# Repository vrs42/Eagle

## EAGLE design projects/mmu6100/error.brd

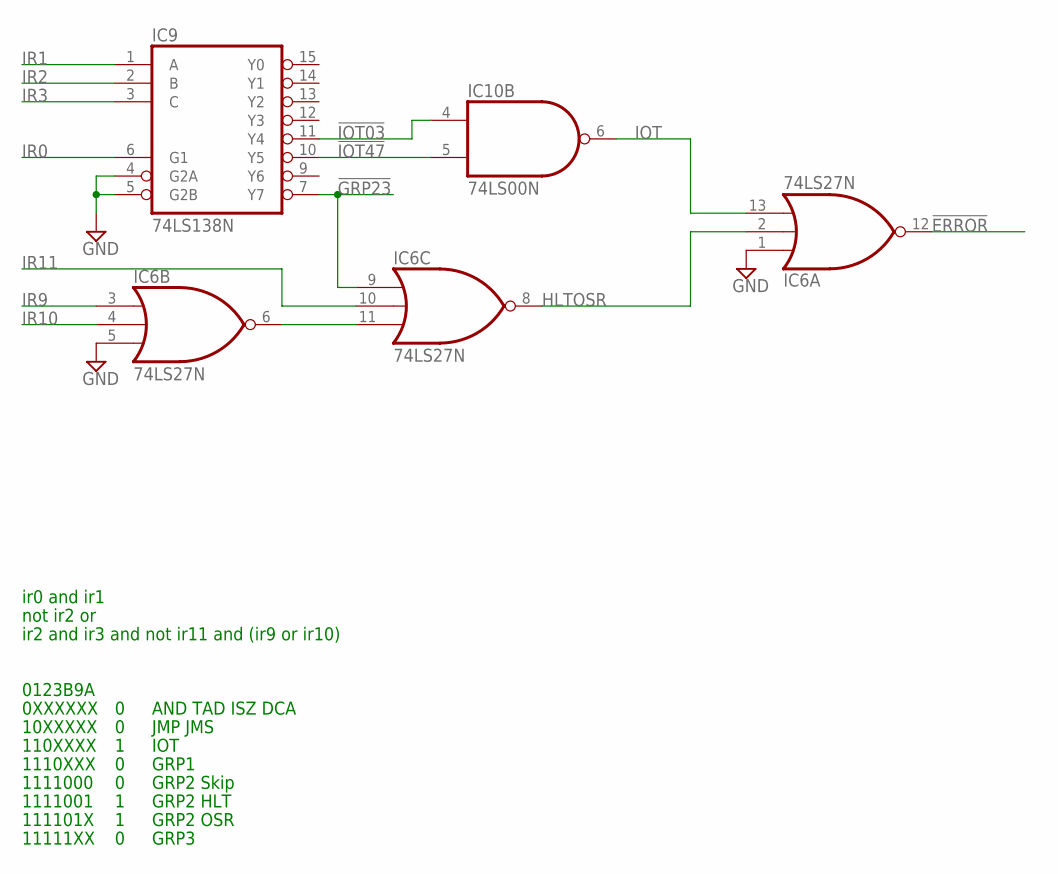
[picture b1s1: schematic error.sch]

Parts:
IC6: 74LS27N; DIL14
IC9: 74LS138N; DIL16
IC10: 74LS00N; DIL14

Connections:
!ERROR: IC6.12 (O)
!GRP23: IC6.9 (I0), IC9.7 (Y7)
!IOT03: IC9.11 (Y4), IC10.4 (I0)
!IOT47: IC9.10 (Y5), IC10.5 (I1)
GND: IC6.1 (I0), IC6.5 (I2), IC6.7 (GND), IC9.4 (G2A), IC9.5 (G2B), IC9.8 (GND), IC10.7 (GND)
HLTOSR: IC6.2 (I1), IC6.8 (O)
IOT: IC6.13 (I2), IC10.6 (O)
IR0: IC9.6 (G1)
IR1: IC9.1 (A)
IR2: IC9.2 (B)
IR3: IC9.3 (C)
IR9: IC6.3 (I0)
IR10: IC6.4 (I1)
IR11: IC6.10 (I1)
unnamed: IC6.6 (O), IC6.11 (I2)
VCC: IC6.14 (VCC), IC9.16 (VCC), IC10.14 (VCC)

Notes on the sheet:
0123B9A
0XXXXXX
10XXXXX
110XXXX
1110XXX
1111000
AND TAD ISZ DCA
JMP JMS
IOT
GRP1
GRP2 Skip
GRP2 OSR
GRP2 HLT
GRP3
1111001
111101X
11111XX
ir0 and ir1
not ir2 or
ir2 and ir3 and not ir11 and (ir9 or ir10)

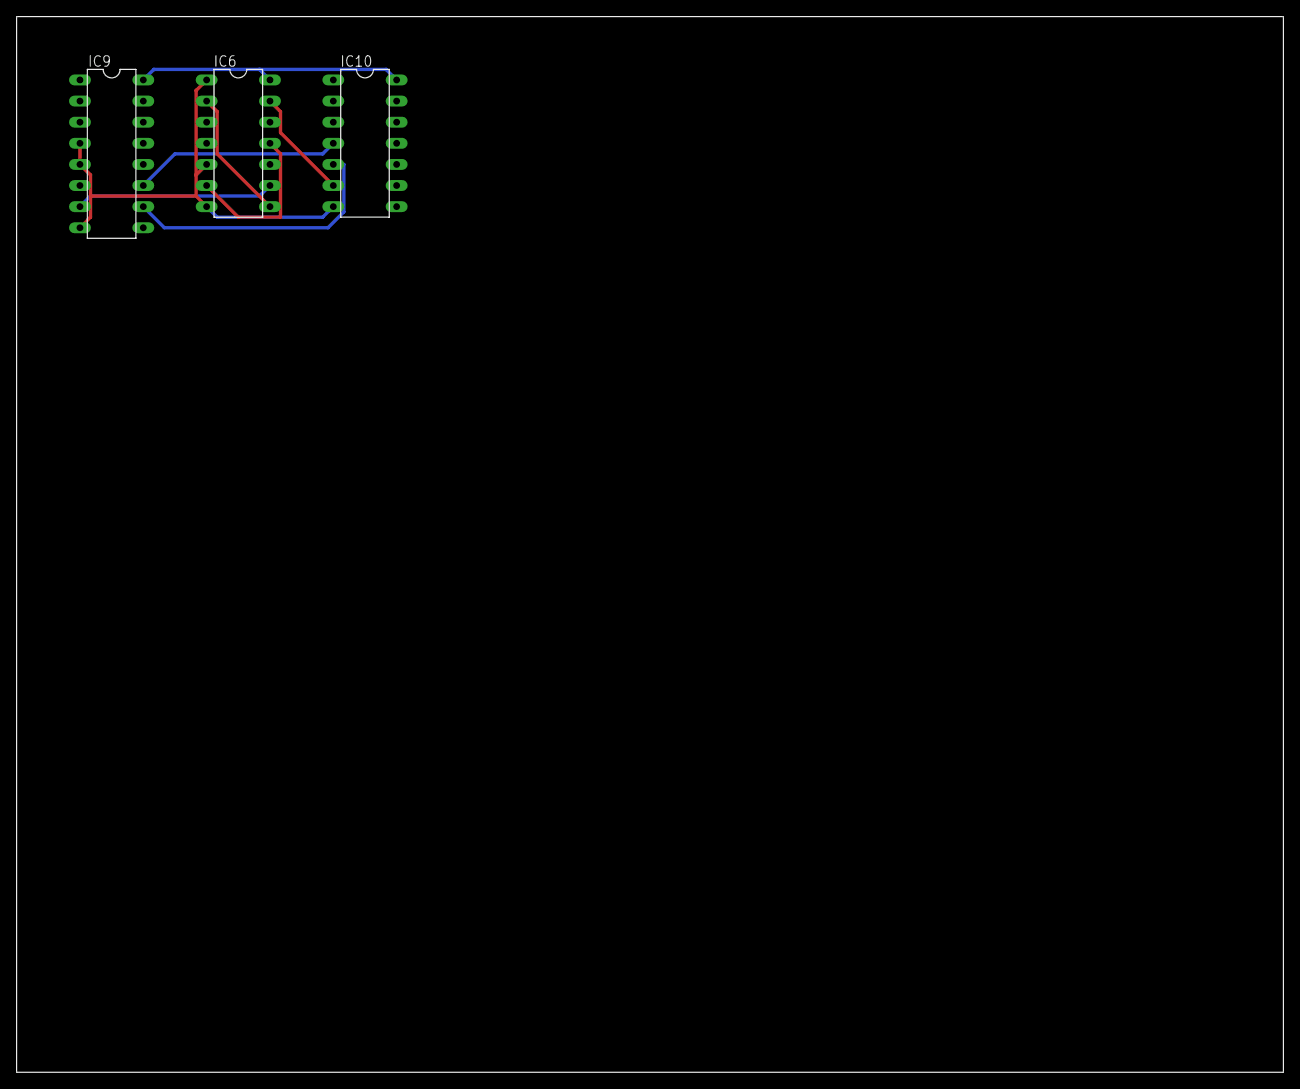
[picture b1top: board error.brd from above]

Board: 2 copper layers, 152.4 x 127.0 mm, 3 parts (0 on the bottom side), 8 nets.

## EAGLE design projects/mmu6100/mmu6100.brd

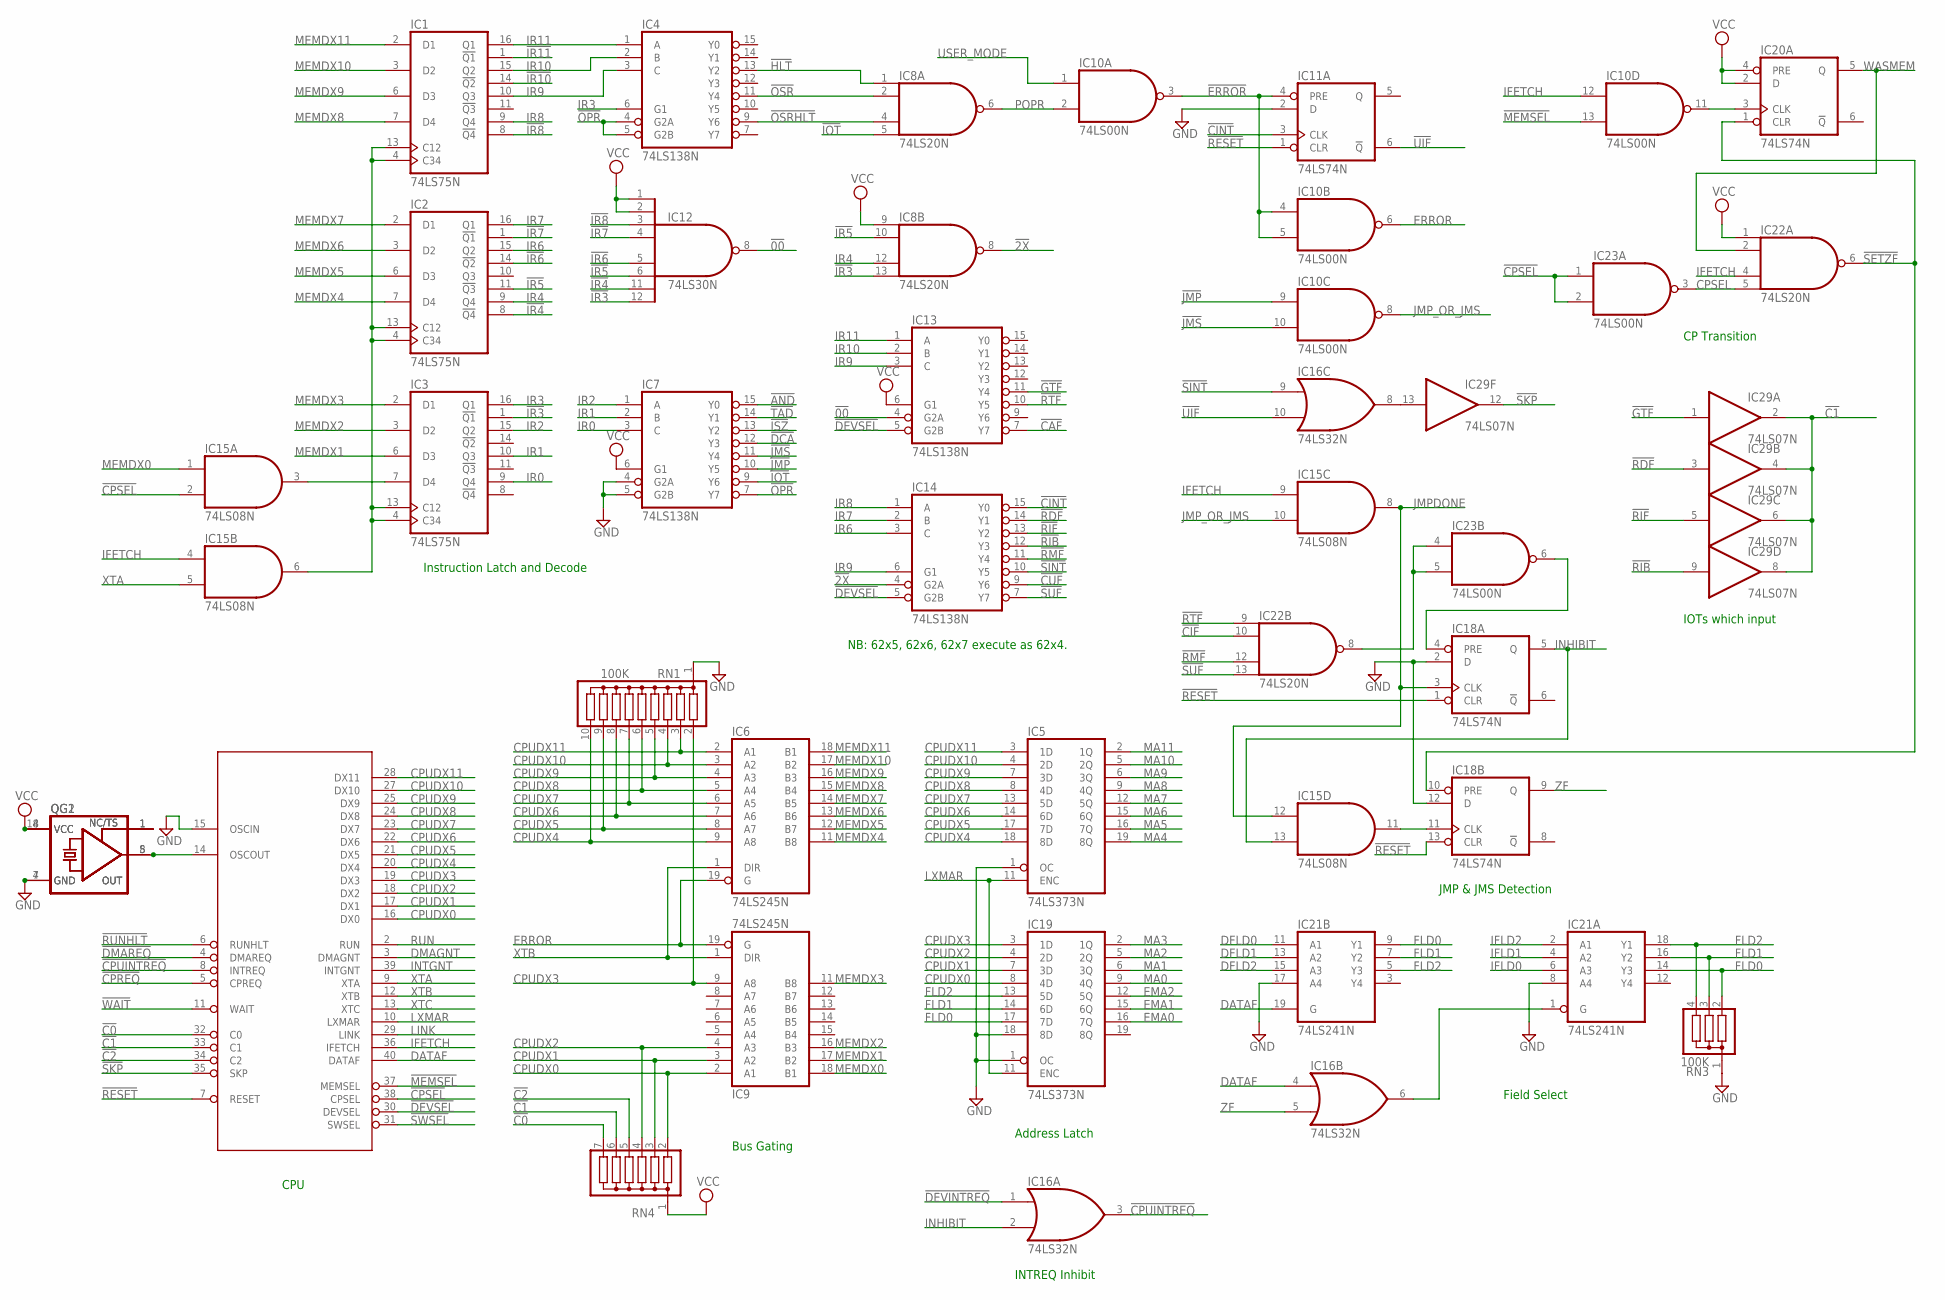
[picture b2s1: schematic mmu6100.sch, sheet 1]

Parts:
CPU: IM6100; DIL40
IC1, IC2, IC3: 74LS75N; DIL16
IC4, IC7, IC13, IC14: 74LS138N; DIL16
IC5, IC19: 74LS373N; DIL20
IC6, IC9: 74LS245N; DIL20
IC8, IC22: 74LS20N; DIL14
IC10, IC23: 74LS00N; DIL14
IC11, IC18, IC20: 74LS74N; DIL14
IC12: 74LS30N; DIL14
IC15: 74LS08N; DIL14
IC16: 74LS32N; DIL14
IC21: 74LS241N; DIL20
IC29: 74LS07N; DIL14
QG1: XO-8; DIL08S
QG2: XO-14; DIL14S
RN1: 100K; SIL10
RN3: 100K; SIL4
RN4: G06R; SIL7

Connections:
!00: IC12.8 (O), IC13.4 (G2A)
!2X: IC8.8 (O), IC14.4 (G2A); also elsewhere on the board
!AND: IC7.15 (Y0); also elsewhere on the board
!C0: CPU.32 (C0), RN4.7; also elsewhere on the board
!C1: CPU.33 (C1), IC29.2 (O), IC29.4 (O), IC29.6 (O), IC29.8 (O), RN4.6; also elsewhere on the board
!C2: CPU.34 (C2), RN4.5; also elsewhere on the board
!CAF: IC13.7 (Y7); also elsewhere on the board
!CIF: IC22.10 (I1); also elsewhere on the board
!CINT: IC11.3 (CLK), IC14.15 (Y0)
!CPREQ: CPU.5 (CPREQ); also elsewhere on the board
!CPSEL: CPU.38 (CPSEL), IC15.2 (I1), IC23.1 (I0), IC23.2 (I1)
!CPUINTREQ: CPU.8 (INTREQ), IC16.3 (O)
!CUF: IC14.9 (Y6); also elsewhere on the board
!DCA: IC7.12 (Y3); also elsewhere on the board
!DEVINTREQ: IC16.1 (I0); also elsewhere on the board
!DEVSEL: CPU.30 (DEVSEL), IC13.5 (G2B), IC14.5 (G2B); also elsewhere on the board
!DMAREQ: CPU.4 (DMAREQ); also elsewhere on the board
!ERROR: IC10.3 (O), IC10.4 (I0), IC10.5 (I1), IC11.4 (PRE)
!GTF: IC13.11 (Y4), IC29.1 (I); also elsewhere on the board
!HLT: IC4.13 (Y2), IC8.1 (I0)
!IOT: IC7.9 (Y6), IC8.5 (I3); also elsewhere on the board
!IR3: IC3.1 (!Q1), IC8.13 (I3), IC12.12 (I7)
!IR4: IC2.8 (!Q4), IC12.11 (I6)
!IR5: IC2.11 (!Q3), IC8.10 (I1), IC12.6 (I5)
!IR6: IC2.14 (!Q2), IC12.5 (I4)
!IR7: IC2.1 (!Q1), IC12.4 (I3)
!IR8: IC1.8 (!Q4), IC12.3 (I2)
!IR10: IC1.14 (!Q2); also elsewhere on the board
!IR11: IC1.1 (!Q1); also elsewhere on the board
!ISZ: IC7.13 (Y2); also elsewhere on the board
!JMP: IC7.10 (Y5), IC10.9 (I0)
!JMS: IC7.11 (Y4), IC10.10 (I1)
!MEMSEL: CPU.37 (MEMSEL), IC10.13 (I1); also elsewhere on the board
!OPR: IC4.4 (G2A), IC4.5 (G2B), IC7.7 (Y7)
!OSR: IC4.11 (Y4), IC8.2 (I1)
!OSRHLT: IC4.9 (Y6), IC8.4 (I2)
!RDF: IC14.14 (Y1), IC29.3 (I); also elsewhere on the board
!RESET: CPU.7 (RESET), IC11.1 (CLR), IC18.1 (CLR), IC18.13 (CLR); also elsewhere on the board
!RIB: IC14.12 (Y3), IC29.9 (I); also elsewhere on the board
!RIF: IC14.13 (Y2), IC29.5 (I); also elsewhere on the board
!RMF: IC14.11 (Y4), IC22.12 (I2); also elsewhere on the board
!RTF: IC13.10 (Y5), IC22.9 (I0); also elsewhere on the board
!RUNHLT: CPU.6 (RUNHLT); also elsewhere on the board
!SETZF: IC18.10 (PRE), IC20.1 (CLR), IC22.6 (O)
!SINT: IC14.10 (Y5), IC16.9 (I0)
!SKP: CPU.35 (SKP), IC29.12 (O); also elsewhere on the board
!SUF: IC14.7 (Y7), IC22.13 (I3); also elsewhere on the board
!SWSEL: CPU.31 (SWSEL); also elsewhere on the board
!TAD: IC7.14 (Y1); also elsewhere on the board
!UIF: IC11.6 (!Q), IC16.10 (I1)
!WAIT: CPU.11 (WAIT); also elsewhere on the board
CPSEL: IC22.5 (I3), IC23.3 (O)
CPUDX0: CPU.16 (DX0), IC9.2 (A1), IC19.8 (4D), RN4.2; also elsewhere on the board
CPUDX1: CPU.17 (DX1), IC9.3 (A2), IC19.7 (3D), RN4.3; also elsewhere on the board
CPUDX2: CPU.18 (DX2), IC9.4 (A3), IC19.4 (2D), RN4.4; also elsewhere on the board
CPUDX3: CPU.19 (DX3), IC9.9 (A8), IC19.3 (1D), RN1.2; also elsewhere on the board
CPUDX4: CPU.20 (DX4), IC5.18 (8D), IC6.9 (A8), RN1.10; also elsewhere on the board
CPUDX5: CPU.21 (DX5), IC5.17 (7D), IC6.8 (A7), RN1.9; also elsewhere on the board
CPUDX6: CPU.22 (DX6), IC5.14 (6D), IC6.7 (A6), RN1.8; also elsewhere on the board
CPUDX7: CPU.23 (DX7), IC5.13 (5D), IC6.6 (A5), RN1.7; also elsewhere on the board
CPUDX8: CPU.24 (DX8), IC5.8 (4D), IC6.5 (A4), RN1.6; also elsewhere on the board
CPUDX9: CPU.25 (DX9), IC5.7 (3D), IC6.4 (A3), RN1.5; also elsewhere on the board
CPUDX10: CPU.27 (DX10), IC5.4 (2D), IC6.3 (A2), RN1.4; also elsewhere on the board
CPUDX11: CPU.28 (DX11), IC5.3 (1D), IC6.2 (A1), RN1.3; also elsewhere on the board
DATAF: CPU.40 (DATAF), IC16.4 (I0), IC21.19 (G)
DFLD0: IC21.11 (A1); also elsewhere on the board
DFLD1: IC21.13 (A2); also elsewhere on the board
DFLD2: IC21.15 (A3); also elsewhere on the board
DMAGNT: CPU.3 (DMAGNT); also elsewhere on the board
EMA0: IC19.16 (7Q); also elsewhere on the board
EMA1: IC19.15 (6Q); also elsewhere on the board
EMA2: IC19.12 (5Q); also elsewhere on the board
ERROR: IC6.19 (G), IC9.19 (G), IC10.6 (O)
FLD0: IC19.17 (7D), IC21.9 (Y1), IC21.14 (Y3), RN3.2
FLD1: IC19.14 (6D), IC21.7 (Y2), IC21.16 (Y2), RN3.3
FLD2: IC19.13 (5D), IC21.5 (Y3), IC21.18 (Y1), RN3.4
GND: CPU.15 (OSCIN), CPU.26 (GND), IC1.12 (GND), IC2.12 (GND), IC3.12 (GND), IC4.8 (GND), IC5.1 (OC), IC5.10 (GND), IC6.10 (GND), IC7.4 (G2A), IC7.5 (G2B), IC7.8 (GND), IC8.7 (GND), IC9.10 (GND), IC10.7 (GND), IC11.2 (D), IC11.7 (GND), IC12.7 (GND), IC13.8 (GND), IC14.8 (GND), IC15.7 (GND), IC16.7 (GND), IC18.2 (D), IC18.7 (GND), IC18.12 (D), IC19.1 (OC), IC19.10 (GND), IC19.18 (8D), IC20.7 (GND), IC21.8 (A4), IC21.10 (GND), IC21.17 (A4), IC22.7 (GND), IC23.7 (GND), IC29.7 (GND), QG1.4 (GND), QG2.7 (GND), RN1.1, RN3.1; also elsewhere on the board
IFETCH: CPU.36 (IFETCH), IC10.12 (I0), IC15.4 (I0), IC15.9 (I0), IC22.4 (I2)
IFLD0: IC21.6 (A3); also elsewhere on the board
IFLD1: IC21.4 (A2); also elsewhere on the board
IFLD2: IC21.2 (A1); also elsewhere on the board
INHIBIT: IC15.13 (I1), IC16.2 (I1), IC18.5 (Q); also elsewhere on the board
INTGNT: CPU.39 (INTGNT); also elsewhere on the board
IR0: IC3.9 (Q4), IC7.3 (C)
IR1: IC3.10 (Q3), IC7.2 (B)
IR2: IC3.15 (Q2), IC7.1 (A)
IR3: IC3.16 (Q1), IC4.6 (G1)
IR4: IC2.9 (Q4), IC8.12 (I2)
IR6: IC2.15 (Q2), IC14.3 (C); also elsewhere on the board
IR7: IC2.16 (Q1), IC14.2 (B); also elsewhere on the board
IR8: IC1.9 (Q4), IC14.1 (A); also elsewhere on the board
IR9: IC1.10 (Q3), IC4.3 (C), IC13.3 (C), IC14.6 (G1); also elsewhere on the board
IR10: IC1.15 (Q2), IC4.2 (B), IC13.2 (B)
IR11: IC1.16 (Q1), IC4.1 (A), IC13.1 (A)
JMPDONE: IC15.8 (O), IC15.12 (I0), IC18.3 (CLK); also elsewhere on the board
JMP_OR_JMS: IC10.8 (O), IC15.10 (I1)
LINK: CPU.29 (LINK); also elsewhere on the board
LXMAR: CPU.10 (LXMAR), IC5.11 (ENC), IC19.11 (ENC); also elsewhere on the board
MA0: IC19.9 (4Q); also elsewhere on the board
MA1: IC19.6 (3Q); also elsewhere on the board
MA2: IC19.5 (2Q); also elsewhere on the board
MA3: IC19.2 (1Q); also elsewhere on the board
MA4: IC5.19 (8Q); also elsewhere on the board
MA5: IC5.16 (7Q); also elsewhere on the board
MA6: IC5.15 (6Q); also elsewhere on the board
MA7: IC5.12 (5Q); also elsewhere on the board
MA8: IC5.9 (4Q); also elsewhere on the board
MA9: IC5.6 (3Q); also elsewhere on the board
MA10: IC5.5 (2Q); also elsewhere on the board
MA11: IC5.2 (1Q); also elsewhere on the board
MEMDX0: IC9.18 (B1), IC15.1 (I0); also elsewhere on the board
MEMDX1: IC3.6 (D3), IC9.17 (B2); also elsewhere on the board
MEMDX2: IC3.3 (D2), IC9.16 (B3); also elsewhere on the board
MEMDX3: IC3.2 (D1), IC9.11 (B8); also elsewhere on the board
MEMDX4: IC2.7 (D4), IC6.11 (B8); also elsewhere on the board
MEMDX5: IC2.6 (D3), IC6.12 (B7); also elsewhere on the board
MEMDX6: IC2.3 (D2), IC6.13 (B6); also elsewhere on the board
MEMDX7: IC2.2 (D1), IC6.14 (B5); also elsewhere on the board
MEMDX8: IC1.7 (D4), IC6.15 (B4); also elsewhere on the board
MEMDX9: IC1.6 (D3), IC6.16 (B3); also elsewhere on the board
MEMDX10: IC1.3 (D2), IC6.17 (B2); also elsewhere on the board
MEMDX11: IC1.2 (D1), IC6.18 (B1); also elsewhere on the board
unnamed: QG1.1 (TS), QG2.1 (TS)
unnamed: IC1.4 (C34), IC1.13 (C12), IC2.4 (C34), IC2.13 (C12), IC3.4 (C34), IC3.13 (C12), IC15.6 (O)
unnamed: IC15.11 (O), IC18.11 (CLK)
unnamed: IC10.11 (O), IC20.3 (CLK)
unnamed: IC16.6 (O), IC21.1 (G)
unnamed: IC3.7 (D4), IC15.3 (O)
unnamed: IC16.8 (O), IC29.13 (I)
unnamed: IC22.8 (O), IC23.4 (I0), IC23.5 (I1)
unnamed: IC18.4 (PRE), IC23.6 (O)
OSCOUT: CPU.14 (OSCOUT), QG1.5 (OUT), QG2.8 (OUT)
POPR: IC8.6 (O), IC10.2 (I1)
RUN: CPU.2 (RUN); also elsewhere on the board
USER_MODE: IC10.1 (I0); also elsewhere on the board
VCC: CPU.1 (VCC), IC1.5 (VCC), IC2.5 (VCC), IC3.5 (VCC), IC4.16 (VCC), IC5.20 (VCC), IC6.20 (VCC), IC7.6 (G1), IC7.16 (VCC), IC8.9 (I0), IC8.14 (VCC), IC9.20 (VCC), IC10.14 (VCC), IC11.14 (VCC), IC12.1 (I0), IC12.2 (I1), IC12.14 (VCC), IC13.6 (G1), IC13.16 (VCC), IC14.16 (VCC), IC15.14 (VCC), IC16.14 (VCC), IC18.14 (VCC), IC19.20 (VCC), IC20.2 (D), IC20.4 (PRE), IC20.14 (VCC), IC21.20 (VCC), IC22.1 (I0), IC22.14 (VCC), IC23.14 (VCC), IC29.14 (VCC), QG1.8 (VCC), QG2.14 (VCC), RN4.1; also elsewhere on the board
WASMEM: IC20.5 (Q), IC22.2 (I1)
XTA: CPU.9 (XTA), IC15.5 (I1); also elsewhere on the board
XTB: CPU.12 (XTB), IC6.1 (DIR), IC9.1 (DIR); also elsewhere on the board
XTC: CPU.13 (XTC); also elsewhere on the board
ZF: IC16.5 (I1), IC18.9 (Q)

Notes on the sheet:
Instruction Latch and Decode
CPU
Bus Gating
Field Select
Address Latch
INTREQ Inhibit
JMP & JMS Detection
CP Transition
IOTs which input
NB: 62x5, 62x6, 62x7 execute as 62x4.

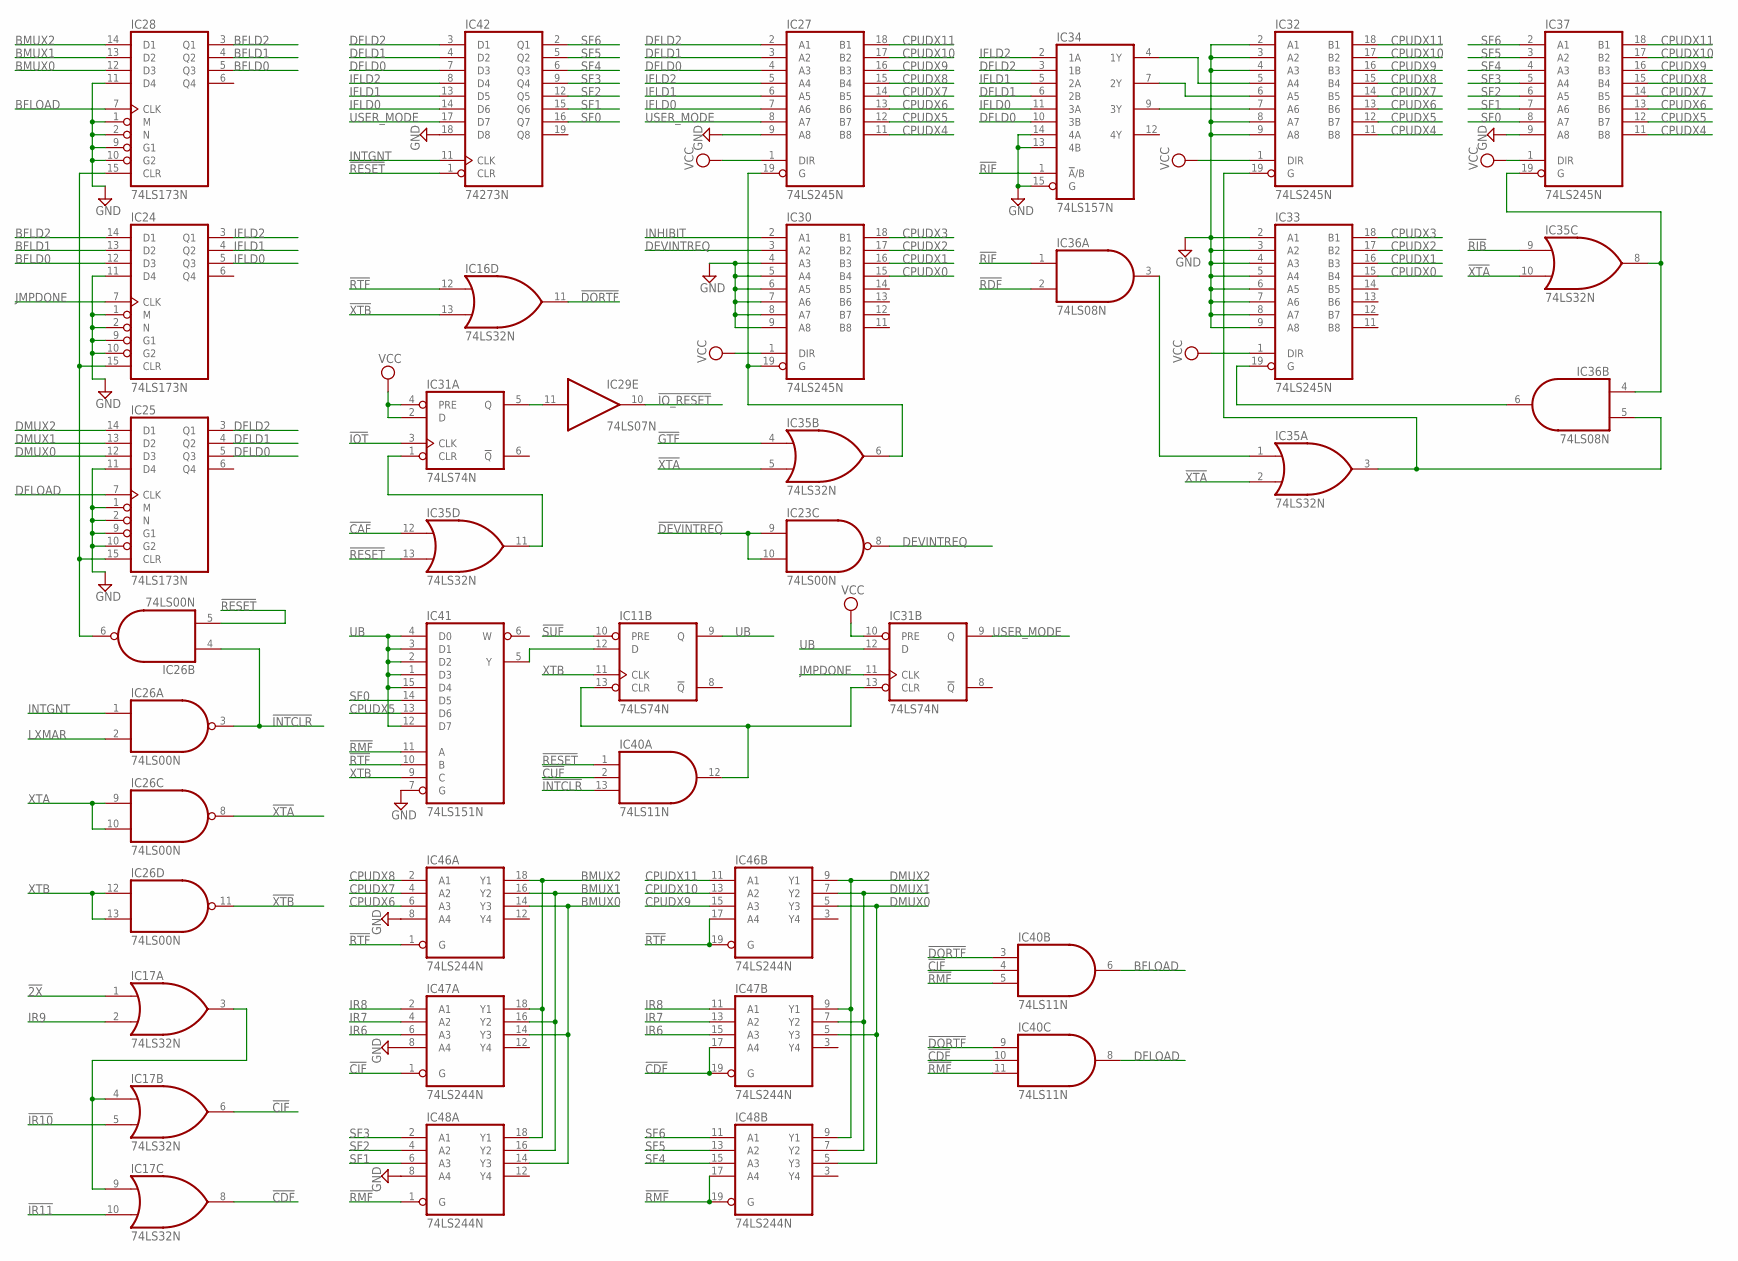
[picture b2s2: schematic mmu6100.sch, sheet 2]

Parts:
IC11, IC31: 74LS74N; DIL14
IC16, IC17, IC35: 74LS32N; DIL14
IC23, IC26: 74LS00N; DIL14
IC24, IC25, IC28: 74LS173N; DIL16
IC27, IC30, IC32, IC33, IC37: 74LS245N; DIL20
IC29: 74LS07N; DIL14
IC34: 74LS157N; DIL16
IC36: 74LS08N; DIL14
IC40: 74LS11N; DIL14
IC41: 74LS151N; DIL16
IC42: 74273N; DIL20
IC46, IC47, IC48: 74LS244N; DIL20

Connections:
!2X: IC17.1 (I0); also elsewhere on the board
!CAF: IC35.12 (I0); also elsewhere on the board
!CDF: IC17.8 (O), IC40.10 (I1), IC47.17 (A4), IC47.19 (G)
!CIF: IC17.6 (O), IC40.4 (I1), IC47.1 (G); also elsewhere on the board
!CUF: IC40.2 (I1); also elsewhere on the board
!DEVINTREQ: IC23.9 (I0), IC23.10 (I1); also elsewhere on the board
!DORTF: IC16.11 (O), IC40.3 (I0), IC40.9 (I0)
!GTF: IC35.4 (I0); also elsewhere on the board
!INTCLR: IC26.3 (O), IC26.4 (I0), IC40.13 (I2)
!IOT: IC31.3 (CLK); also elsewhere on the board
!IO_RESET: IC29.10 (O); also elsewhere on the board
!IR10: IC17.5 (I1); also elsewhere on the board
!IR11: IC17.10 (I1); also elsewhere on the board
!RDF: IC36.2 (I1); also elsewhere on the board
!RESET: IC26.5 (I1), IC35.13 (I1), IC40.1 (I0), IC42.1 (CLR); also elsewhere on the board
!RIB: IC35.9 (I0); also elsewhere on the board
!RIF: IC34.1 (!A!/B), IC36.1 (I0); also elsewhere on the board
!RMF: IC40.5 (I2), IC40.11 (I2), IC41.11 (A), IC48.1 (G), IC48.17 (A4), IC48.19 (G); also elsewhere on the board
!RTF: IC16.12 (I0), IC41.10 (B), IC46.1 (G), IC46.17 (A4), IC46.19 (G); also elsewhere on the board
!SUF: IC11.10 (PRE); also elsewhere on the board
!XTA: IC26.8 (O), IC35.2 (I1), IC35.5 (I1), IC35.10 (I1); also elsewhere on the board
!XTB: IC16.13 (I1), IC26.11 (O); also elsewhere on the board
BFLD0: IC24.12 (D3), IC28.5 (Q3)
BFLD1: IC24.13 (D2), IC28.4 (Q2)
BFLD2: IC24.14 (D1), IC28.3 (Q1)
BFLOAD: IC28.7 (CLK), IC40.6 (O)
BMUX0: IC28.12 (D3), IC46.14 (Y3), IC47.14 (Y3), IC48.14 (Y3)
BMUX1: IC28.13 (D2), IC46.16 (Y2), IC47.16 (Y2), IC48.16 (Y2)
BMUX2: IC28.14 (D1), IC46.18 (Y1), IC47.18 (Y1), IC48.18 (Y1)
CPUDX0: IC30.15 (B4), IC33.15 (B4); also elsewhere on the board
CPUDX1: IC30.16 (B3), IC33.16 (B3); also elsewhere on the board
CPUDX2: IC30.17 (B2), IC33.17 (B2); also elsewhere on the board
CPUDX3: IC30.18 (B1), IC33.18 (B1); also elsewhere on the board
CPUDX4: IC27.11 (B8), IC32.11 (B8), IC37.11 (B8); also elsewhere on the board
CPUDX5: IC27.12 (B7), IC32.12 (B7), IC37.12 (B7), IC41.13 (D6); also elsewhere on the board
CPUDX6: IC27.13 (B6), IC32.13 (B6), IC37.13 (B6), IC46.6 (A3); also elsewhere on the board
CPUDX7: IC27.14 (B5), IC32.14 (B5), IC37.14 (B5), IC46.4 (A2); also elsewhere on the board
CPUDX8: IC27.15 (B4), IC32.15 (B4), IC37.15 (B4), IC46.2 (A1); also elsewhere on the board
CPUDX9: IC27.16 (B3), IC32.16 (B3), IC37.16 (B3), IC46.15 (A3); also elsewhere on the board
CPUDX10: IC27.17 (B2), IC32.17 (B2), IC37.17 (B2), IC46.13 (A2); also elsewhere on the board
CPUDX11: IC27.18 (B1), IC32.18 (B1), IC37.18 (B1), IC46.11 (A1); also elsewhere on the board
DEVINTREQ: IC23.8 (O), IC30.3 (A2)
DFLD0: IC25.5 (Q3), IC27.4 (A3), IC34.10 (3B), IC42.7 (D3); also elsewhere on the board
DFLD1: IC25.4 (Q2), IC27.3 (A2), IC34.6 (2B), IC42.4 (D2); also elsewhere on the board
DFLD2: IC25.3 (Q1), IC27.2 (A1), IC34.3 (1B), IC42.3 (D1); also elsewhere on the board
DFLOAD: IC25.7 (CLK), IC40.8 (O)
DMUX0: IC25.12 (D3), IC46.5 (Y3), IC47.5 (Y3), IC48.5 (Y3)
DMUX1: IC25.13 (D2), IC46.7 (Y2), IC47.7 (Y2), IC48.7 (Y2)
DMUX2: IC25.14 (D1), IC46.9 (Y1), IC47.9 (Y1), IC48.9 (Y1)
GND: IC11.7 (GND), IC16.7 (GND), IC17.7 (GND), IC23.7 (GND), IC24.1 (M), IC24.2 (N), IC24.8 (GND), IC24.9 (G1), IC24.10 (G2), IC24.11 (D4), IC25.1 (M), IC25.2 (N), IC25.8 (GND), IC25.9 (G1), IC25.10 (G2), IC25.11 (D4), IC26.7 (GND), IC27.9 (A8), IC27.10 (GND), IC28.1 (M), IC28.2 (N), IC28.8 (GND), IC28.9 (G1), IC28.10 (G2), IC28.11 (D4), IC29.7 (GND), IC30.4 (A3), IC30.5 (A4), IC30.6 (A5), IC30.7 (A6), IC30.8 (A7), IC30.9 (A8), IC30.10 (GND), IC31.7 (GND), IC32.2 (A1), IC32.3 (A2), IC32.4 (A3), IC32.8 (A7), IC32.9 (A8), IC32.10 (GND), IC33.2 (A1), IC33.3 (A2), IC33.4 (A3), IC33.5 (A4), IC33.6 (A5), IC33.7 (A6), IC33.8 (A7), IC33.9 (A8), IC33.10 (GND), IC34.8 (GND), IC34.13 (4B), IC34.14 (4A), IC34.15 (G), IC35.7 (GND), IC36.7 (GND), IC37.9 (A8), IC37.10 (GND), IC40.7 (GND), IC41.7 (G), IC41.8 (GND), IC42.10 (GND), IC42.18 (D8), IC46.8 (A4), IC46.10 (GND), IC47.8 (A4), IC47.10 (GND), IC48.8 (A4), IC48.10 (GND); also elsewhere on the board
IFLD0: IC24.5 (Q3), IC27.7 (A6), IC34.11 (3A), IC42.14 (D6); also elsewhere on the board
IFLD1: IC24.4 (Q2), IC27.6 (A5), IC34.5 (2A), IC42.13 (D5); also elsewhere on the board
IFLD2: IC24.3 (Q1), IC27.5 (A4), IC34.2 (1A), IC42.8 (D4); also elsewhere on the board
INHIBIT: IC30.2 (A1); also elsewhere on the board
INTCLR: IC24.15 (CLR), IC25.15 (CLR), IC26.6 (O), IC28.15 (CLR)
INTGNT: IC26.1 (I0), IC42.11 (CLK); also elsewhere on the board
IR6: IC47.6 (A3), IC47.15 (A3); also elsewhere on the board
IR7: IC47.4 (A2), IC47.13 (A2); also elsewhere on the board
IR8: IC47.2 (A1), IC47.11 (A1); also elsewhere on the board
IR9: IC17.2 (I1); also elsewhere on the board
JMPDONE: IC24.7 (CLK), IC31.11 (CLK); also elsewhere on the board
LXMAR: IC26.2 (I1); also elsewhere on the board
unnamed: IC27.19 (G), IC30.19 (G), IC35.6 (O)
unnamed: IC29.11 (I), IC31.5 (Q)
unnamed: IC32.19 (G), IC35.3 (O), IC36.5 (I1)
unnamed: IC35.8 (O), IC36.4 (I0), IC37.19 (G)
unnamed: IC32.5 (A4), IC34.4 (1Y)
unnamed: IC32.6 (A5), IC34.7 (2Y)
unnamed: IC32.7 (A6), IC34.9 (3Y)
unnamed: IC35.1 (I0), IC36.3 (O)
unnamed: IC33.19 (G), IC36.6 (O)
unnamed: IC11.13 (CLR), IC31.13 (CLR), IC40.12 (O)
unnamed: IC11.12 (D), IC41.5 (Y)
unnamed: IC31.1 (CLR), IC35.11 (O)
unnamed: IC17.3 (O), IC17.4 (I0), IC17.9 (I0)
SF0: IC37.8 (A7), IC41.14 (D5), IC42.16 (Q7)
SF1: IC37.7 (A6), IC42.15 (Q6), IC48.6 (A3)
SF2: IC37.6 (A5), IC42.12 (Q5), IC48.4 (A2)
SF3: IC37.5 (A4), IC42.9 (Q4), IC48.2 (A1)
SF4: IC37.4 (A3), IC42.6 (Q3), IC48.15 (A3)
SF5: IC37.3 (A2), IC42.5 (Q2), IC48.13 (A2)
SF6: IC37.2 (A1), IC42.2 (Q1), IC48.11 (A1)
UB: IC11.9 (Q), IC31.12 (D), IC41.1 (D3), IC41.2 (D2), IC41.3 (D1), IC41.4 (D0), IC41.12 (D7), IC41.15 (D4)
USER_MODE: IC27.8 (A7), IC31.9 (Q), IC42.17 (D7); also elsewhere on the board
VCC: IC11.14 (VCC), IC16.14 (VCC), IC17.14 (VCC), IC23.14 (VCC), IC24.16 (VCC), IC25.16 (VCC), IC26.14 (VCC), IC27.1 (DIR), IC27.20 (VCC), IC28.16 (VCC), IC29.14 (VCC), IC30.1 (DIR), IC30.20 (VCC), IC31.2 (D), IC31.4 (PRE), IC31.10 (PRE), IC31.14 (VCC), IC32.1 (DIR), IC32.20 (VCC), IC33.1 (DIR), IC33.20 (VCC), IC34.16 (VCC), IC35.14 (VCC), IC36.14 (VCC), IC37.1 (DIR), IC37.20 (VCC), IC40.14 (VCC), IC41.16 (VCC), IC42.20 (VCC), IC46.20 (VCC), IC47.20 (VCC), IC48.20 (VCC); also elsewhere on the board
XTA: IC26.9 (I0), IC26.10 (I1); also elsewhere on the board
XTB: IC11.11 (CLK), IC26.12 (I0), IC26.13 (I1), IC41.9 (C); also elsewhere on the board

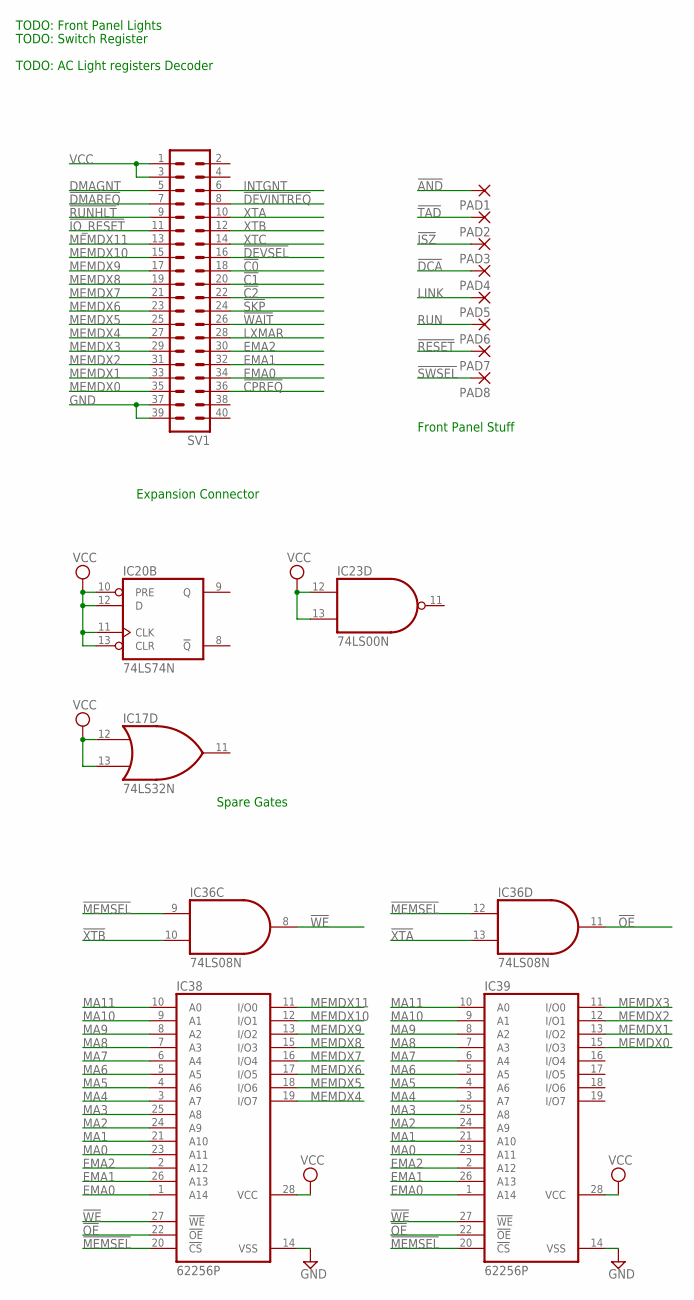
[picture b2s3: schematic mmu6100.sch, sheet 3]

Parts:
IC17: 74LS32N; DIL14
IC20: 74LS74N; DIL14
IC23: 74LS00N; DIL14
IC36: 74LS08N; DIL14
IC38, IC39: 62256P; DIL28-6
PAD1, PAD2, PAD3, PAD4, PAD5, PAD6, PAD7, PAD8: 2,15/1,0
SV1: MA20-2

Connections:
!AND: PAD1.1; also elsewhere on the board
!C0: SV1.18; also elsewhere on the board
!C1: SV1.20; also elsewhere on the board
!C2: SV1.22; also elsewhere on the board
!CPREQ: SV1.36; also elsewhere on the board
!DCA: PAD4.1; also elsewhere on the board
!DEVINTREQ: SV1.8; also elsewhere on the board
!DEVSEL: SV1.16; also elsewhere on the board
!DMAREQ: SV1.7; also elsewhere on the board
!IO_RESET: SV1.11; also elsewhere on the board
!ISZ: PAD3.1; also elsewhere on the board
!MEMSEL: IC36.9 (I0), IC36.12 (I0), IC38.20 (!CS), IC39.20 (!CS); also elsewhere on the board
!OE: IC36.11 (O), IC38.22 (!OE), IC39.22 (!OE)
!RESET: PAD7.1; also elsewhere on the board
!RUNHLT: SV1.9; also elsewhere on the board
!SKP: SV1.24; also elsewhere on the board
!SWSEL: PAD8.1; also elsewhere on the board
!TAD: PAD2.1; also elsewhere on the board
!WAIT: SV1.26; also elsewhere on the board
!WE: IC36.8 (O), IC38.27 (!WE), IC39.27 (!WE)
!XTA: IC36.13 (I1); also elsewhere on the board
!XTB: IC36.10 (I1); also elsewhere on the board
DMAGNT: SV1.5; also elsewhere on the board
EMA0: IC38.1 (A14), IC39.1 (A14), SV1.34; also elsewhere on the board
EMA1: IC38.26 (A13), IC39.26 (A13), SV1.32; also elsewhere on the board
EMA2: IC38.2 (A12), IC39.2 (A12), SV1.30; also elsewhere on the board
GND: IC17.7 (GND), IC20.7 (GND), IC23.7 (GND), IC36.7 (GND), IC38.14 (VSS), IC39.14 (VSS), SV1.37, SV1.39; also elsewhere on the board
INTGNT: SV1.6; also elsewhere on the board
LINK: PAD5.1; also elsewhere on the board
LXMAR: SV1.28; also elsewhere on the board
MA0: IC38.23 (A11), IC39.23 (A11); also elsewhere on the board
MA1: IC38.21 (A10), IC39.21 (A10); also elsewhere on the board
MA2: IC38.24 (A9), IC39.24 (A9); also elsewhere on the board
MA3: IC38.25 (A8), IC39.25 (A8); also elsewhere on the board
MA4: IC38.3 (A7), IC39.3 (A7); also elsewhere on the board
MA5: IC38.4 (A6), IC39.4 (A6); also elsewhere on the board
MA6: IC38.5 (A5), IC39.5 (A5); also elsewhere on the board
MA7: IC38.6 (A4), IC39.6 (A4); also elsewhere on the board
MA8: IC38.7 (A3), IC39.7 (A3); also elsewhere on the board
MA9: IC38.8 (A2), IC39.8 (A2); also elsewhere on the board
MA10: IC38.9 (A1), IC39.9 (A1); also elsewhere on the board
MA11: IC38.10 (A0), IC39.10 (A0); also elsewhere on the board
MEMDX0: IC39.15 (I/O3), SV1.35; also elsewhere on the board
MEMDX1: IC39.13 (I/O2), SV1.33; also elsewhere on the board
MEMDX2: IC39.12 (I/O1), SV1.31; also elsewhere on the board
MEMDX3: IC39.11 (I/O0), SV1.29; also elsewhere on the board
MEMDX4: IC38.19 (I/O7), SV1.27; also elsewhere on the board
MEMDX5: IC38.18 (I/O6), SV1.25; also elsewhere on the board
MEMDX6: IC38.17 (I/O5), SV1.23; also elsewhere on the board
MEMDX7: IC38.16 (I/O4), SV1.21; also elsewhere on the board
MEMDX8: IC38.15 (I/O3), SV1.19; also elsewhere on the board
MEMDX9: IC38.13 (I/O2), SV1.17; also elsewhere on the board
MEMDX10: IC38.12 (I/O1), SV1.15; also elsewhere on the board
MEMDX11: IC38.11 (I/O0), SV1.13; also elsewhere on the board
RUN: PAD6.1; also elsewhere on the board
VCC: IC17.12 (I0), IC17.13 (I1), IC17.14 (VCC), IC20.10 (PRE), IC20.11 (CLK), IC20.12 (D), IC20.13 (CLR), IC20.14 (VCC), IC23.12 (I0), IC23.13 (I1), IC23.14 (VCC), IC36.14 (VCC), IC38.28 (VCC), IC39.28 (VCC), SV1.1, SV1.3; also elsewhere on the board
XTA: SV1.10; also elsewhere on the board
XTB: SV1.12; also elsewhere on the board
XTC: SV1.14; also elsewhere on the board

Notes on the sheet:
Expansion Connector
Front Panel Stuff
Spare Gates
TODO: Front Panel Lights
TODO: Switch Register
TODO: AC Light registers Decoder

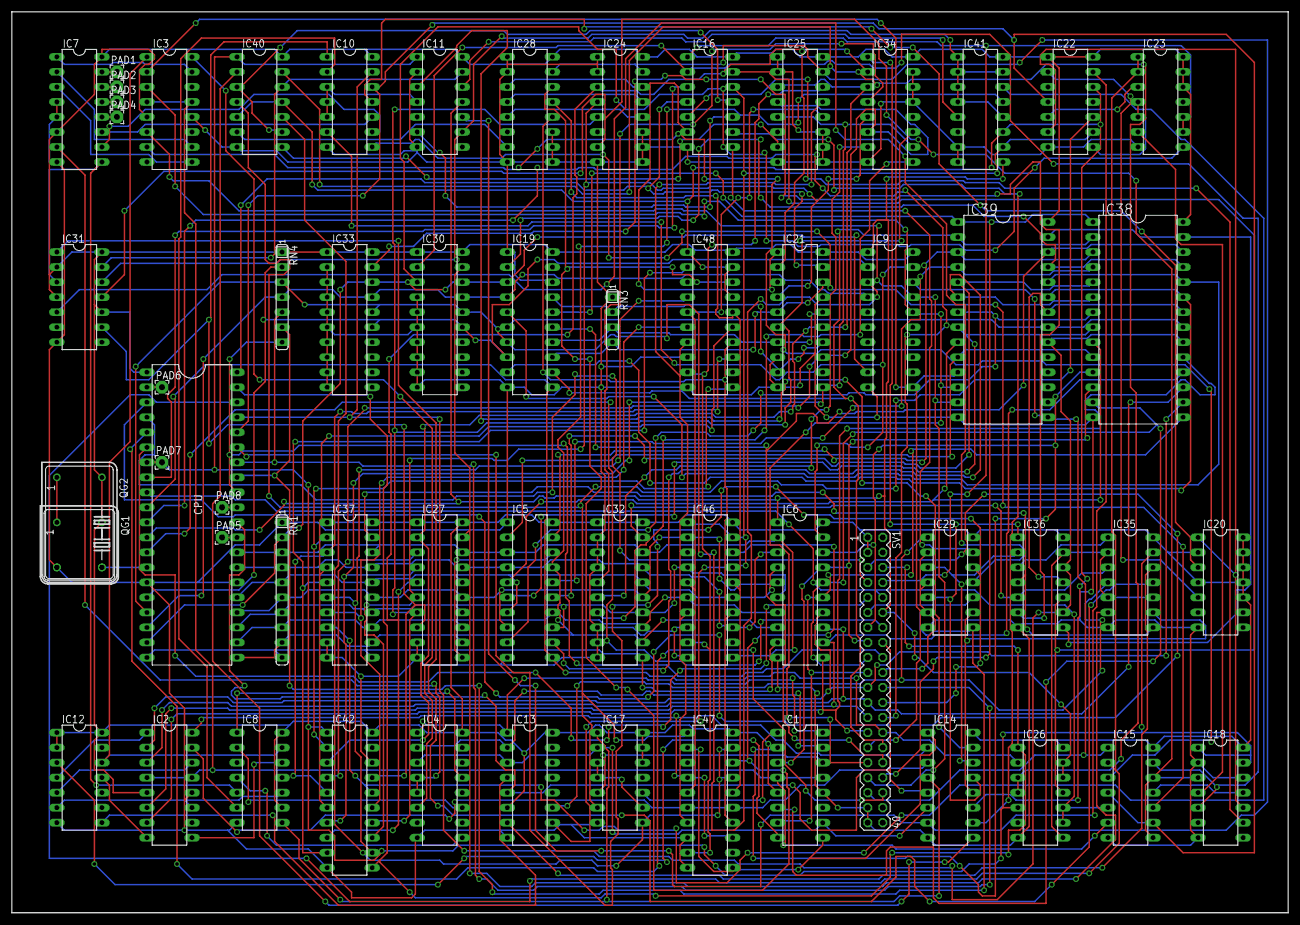
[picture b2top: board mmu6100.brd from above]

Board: 2 copper layers, 215.9 x 152.4 mm, 60 parts (0 on the bottom side), 183 nets.
